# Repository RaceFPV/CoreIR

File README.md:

**What is this?**

CoreIR is an ultra low cost IR timing gate transponder compatible with i-lap rc timing gates. Usually this type of timing system is used for RC car or drone racing to track how fast you can run laps around a track. Using cheap and easy to find hardware, we've seen builds as cheap as $3 per transponder!

*[Now with a detailed build guide!](http://mrickert.com/2016/10/12/building-your-own-coreir-transponder/)*

**What's inside?**

CoreIR comes ready for you to input any 7 digit transponder ID you'd like, just edit the main arduino file's tx_id (CoreIR.ino) to set which transponder ID you would like to have. We have tested with a range from 1111111 to 9999999, but please be aware some id numbers seem to read/perform better than others!

*Don't want to edit arduino files? Use the new [CoreIR-Uplink desktop app!](https://github.com/slacker87/CoreIR-Uplink)*

**Required parts:**
* Arduino pro mini or pro micro (pro micro preferred)
* 9.1 ohm resistor
* npn transistor (2N222 preferred)
* IR led (TSAL6400 preferred)
* Arduino IDE 1.8.3 or higher

**Testing:**

You should see the following once you have built your tranceiver to confirm the code/hardware is working properly...
* Once the firmware is flashed, the led on the arduino should blink two times per second
* If the arduino is blinking around 2x per second, then the code is running correctly
* If the arduino is not blinking, or is blinking seemingly at random, the code needs to be reflashed as the upload failed (or there's a hardware issue)
* With the arduino blinking, point your phone camera at the IR led, the led should be emitting a purple hue
* If you see the purple color from the led on your phone camera, congratulations! Everthing is running smoothly.
* If you do not see any purple hue, but the arduino is blinking steadily, there is a hardware wiring issue or the led has been damaged, check your wiring.

**Wiring:**

##### For micro and pro micro boards:

##### For nano and pro mini boards:

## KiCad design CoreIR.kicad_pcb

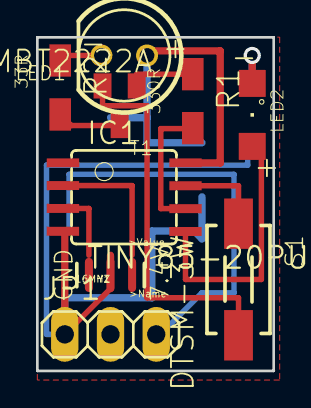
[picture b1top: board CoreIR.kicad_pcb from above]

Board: 2 copper layers, 13.1 x 18.5 mm, 13 parts (0 on the bottom side), 12 nets.

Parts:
C1, C2: 10uF; C1206K
IC1: TINY85-20PU; 8S2
IC2: LD117AS50TR; SOT223
JP1: 1X03
LED1: LED5MM
LED2: SML1206
R1: 330R; R1206W
R2: 33R; R1206W
R3: 100R; R1206W
S1: DTSM-3W
T1: MMBT2222A; SOT23-BEC
Y1: 16MHZ; RESONATOR-SMD

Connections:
5V: C2.1, IC1.8, IC2.4, LED1.A
GND: C1.2, C2.2, IC1.4, IC2.1, JP1.1, R3.2, S1.2, T1.E, Y1.2
unnamed: IC1.5, LED2.A
unnamed: LED1.K, R2.1
unnamed: R2.2, T1.C
unnamed: R1.1, T1.B
unnamed: IC1.6, R1.2
unnamed: LED2.C, R3.1
unnamed: IC1.7, S1.1
unnamed: IC1.3, Y1.3
unnamed: IC1.2, Y1.1
VCC: C1.1, IC2.3, JP1.3

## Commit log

2016-01-29 :neckbeard: Added .gitattributes & .gitignore files
2016-01-29 Add IRremote library package
2016-02-04 add a second transponder
2016-05-10 Add more transponders, also make changing transponder id easier
2016-05-10 Update schematic to reflect better signal distance
2016-05-11 Update schematic part numbers
2016-07-22 Allow use of any transponder number, perform crc and encoding on the fly
2016-07-23 Remove some excess comments
2016-08-15 Remove full IRremote library and insert only required classes, also upload initial kicad drawings of attiny85 board
2016-08-18 Save transponder id in eeprom (prepping for desktop app)
2016-08-18 Add backwards compatibility for attiny devices without eeprom
2016-08-19 Fix for digispark pro
2016-08-19 Implement reading from saved memory, flip defaults for pro micro
2016-08-21 Update irremote library segment
2016-08-22 Fix modulation/freq for arduino micro pro boards, flip it to pin 5, make it more accurate than previous iterations
2016-08-22 Have code auto-detect the arduino board we are using and adjust accordingly (instead of previous manual settings)
2016-08-22 fix a typo
2016-08-23 Use timer1 for atmega328p boards for better accuracy, also blink led different speed for alternate id
2016-08-24 Code cleanup, adjust location for reading bridgein pin
2016-08-24 Continue code cleanup, comment lots of our actions to make code easier to understand
2016-08-24 Flip alt and regular id bridgepin output, clean up send timings so status LED does not fire at same time as IR LED
2016-08-24 Fix an edge case where ID may not get encoded, fix warning about invalid ID #s
2016-08-24 Discover a bitshift bug when generating transponder IDs, causing some IDs to work better than others. Merge IRrem into IRsnd, adjust timings
2016-08-24 Adjust frequency slightly, fix debug for atmega32u4 boards
2016-08-24 Add lots of debug notes in Encode to help display every part of algorithm
2016-08-24 Test new method of transmission via softserial
2016-08-24 Add more debug for sending softserial
2016-08-24 disable softserial mode for now
2016-08-25 Tweak some more timings, fix outputcode array count
2016-08-25 revert some encode tweaks
2016-08-26 Add some test hex files
2016-08-27 Set up loop to allow read/write of transponder ID to eeprom, make new hex
2016-08-27 Resolve an issue with pro micro boards and serial1 hanging
2016-08-29 Update schematic files, update hex files, remove old kicad drawings
2016-09-01 Create LICENSE
2016-09-02 Add initial easyracelaptimer support -- TESTING
2016-09-02 Make easyracelaptimer id and on/off ints so they can be configured by Uplink
2016-09-02 Generate new hex file with easyracelaptimer precompiled
2016-09-02 Give props
2016-09-07 Fix a bug with new easylap compatibility stopping ilap sending
2016-09-28 Rework Board/CPU detection to try and better compile for attiny
2016-10-09 Clean up residule irremote receiver code bits
2016-10-09 Revert "Clean up residule irremote receiver code bits"
    This reverts commit a6e66085ba5983dfa8338248b2632600e50a9f07.
2016-10-09 Pull unused softserial code out, more receiver cleanup
2016-10-09 Change khz rate, remove chips we'll never really use, remove timers never used, remove unused interrupt
2016-10-09 Set khz to 370
2016-10-09 Always use 370khz and 24 frame, always use timer2 if avail
2016-10-10 substantially increase signal range in bright weather conditions
2016-10-10 Update hex file for app
2018-04-04 Clean up ugly hacks for easyracelaptimer option
2018-04-04 Update readme with some basic debugging info
2018-04-04 Overhaul readme formatting
